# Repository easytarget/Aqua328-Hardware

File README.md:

# Controller for a Public (attended) aquarium

See the Full project log on:
https://hackaday.io/project/167871-aqua328-flexible-aquarium-controller

Software is in:
https://github.com/easytarget/Aqua328-Software

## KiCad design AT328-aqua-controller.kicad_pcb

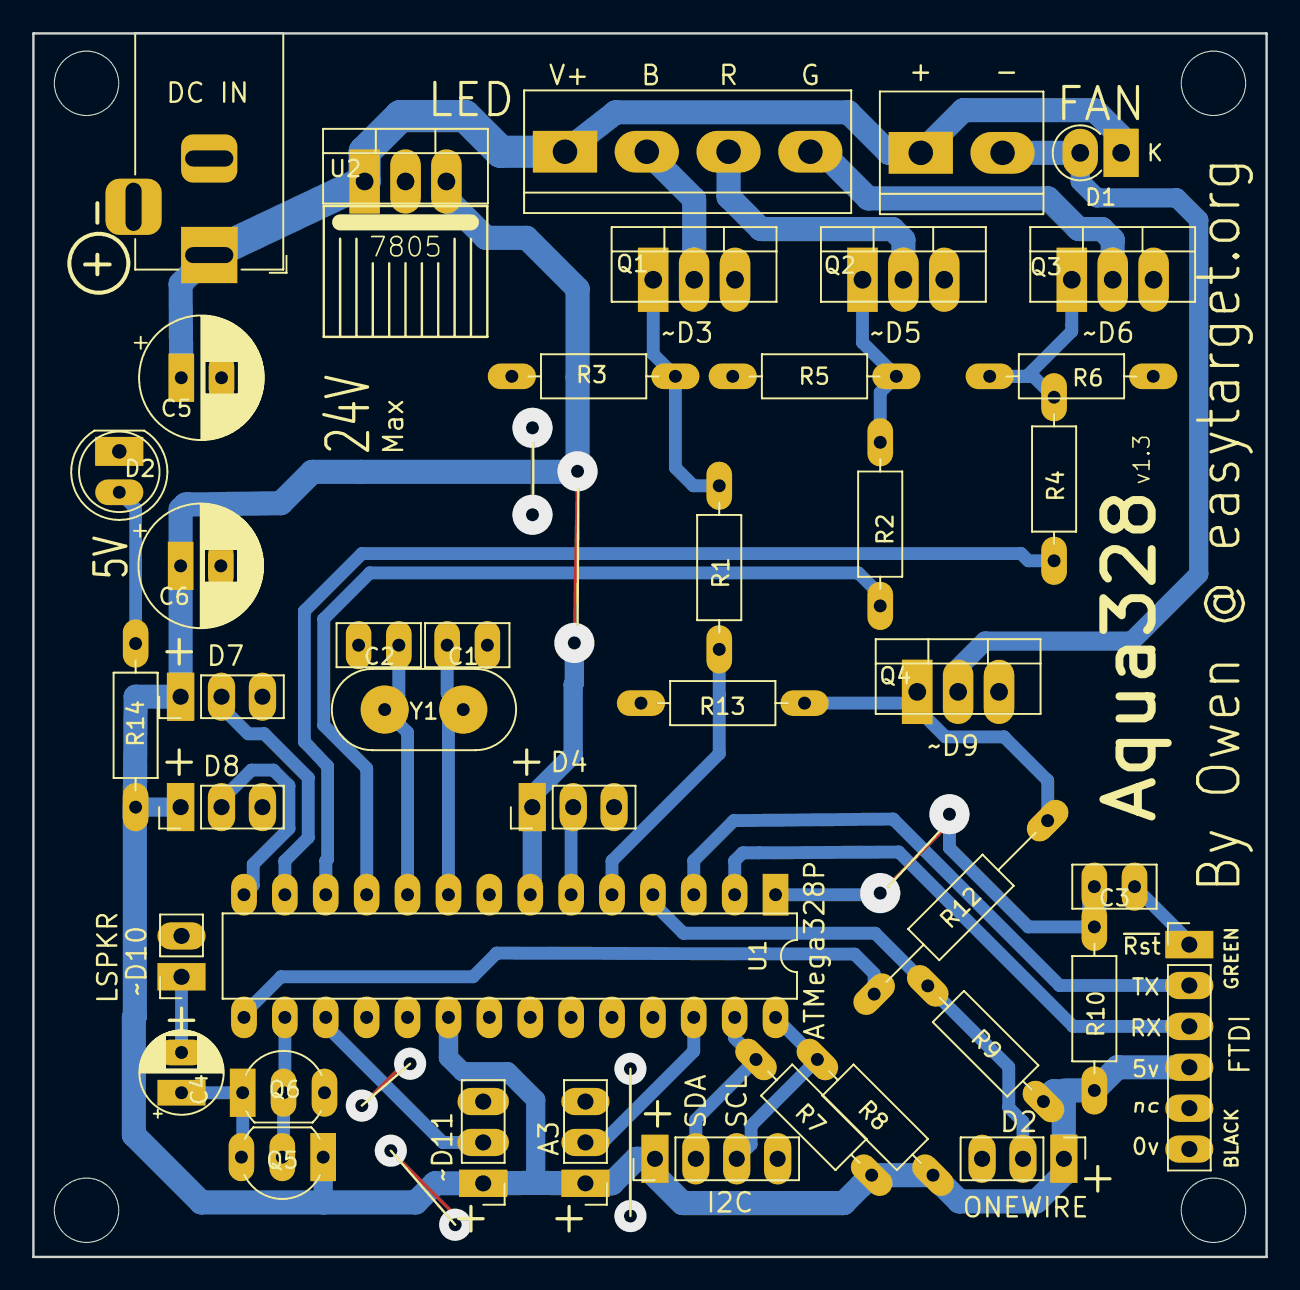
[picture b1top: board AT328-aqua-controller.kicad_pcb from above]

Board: 2 copper layers, 76.6 x 76.0 mm, 46 parts (0 on the bottom side), 33 nets.

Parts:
ABRG_LED1: LED-Strip; TerminalBlock_bornier-4_P5.08mm
AUX1, AUX2, AUX3: Aux Connector; PinHeader_1x03_P2.54mm_Vertical
BUTTON1: Lights/Cycle; PinHeader_1x03_P2.54mm_Vertical
C1, C2: 22p; C_Disc_D5.0mm_W2.5mm_P2.50mm
C3: 100nF; C_Disc_D5.0mm_W2.5mm_P2.50mm
C4: 470uF; CP_Radial_D5.0mm_P2.50mm
C5: 100uF; CP_Radial_D7.5mm_P2.50mm
C6: 22uF; CP_Radial_D7.5mm_P2.50mm
D1: 1N4007; D_DO-41_SOD81_P2.54mm_Vertical_KathodeUp
D2: 5v; LED_D5.0mm
DC_IN1: 12/24v; BarrelJack_Horizontal
FAN1: Fan PWM NPN; TerminalBlock_bornier-2_P5.08mm
FTDI1: FTDI Program Port; PinHeader_1x06_P2.54mm_Vertical
H1, H2, H3, H4: MountingHole; MountingHole_4mm
I2C1: Display; PinHeader_1x04_P2.54mm_Vertical
LID1: Lid Open; PinHeader_1x03_P2.54mm_Vertical
ONEWIRE1: Temp; PinHeader_1x03_P2.54mm_Vertical
Q1, Q2, Q3, Q4: IRL520N; TO-220-3_Vertical
Q5: BC337; TO-92_Inline_Wide
Q6: BC327; TO-92_Inline_Wide
R1, R2, R4, R14: 220R; R_Axial_DIN0207_L6.3mm_D2.5mm_P10.16mm_Horizontal
R3, R5, R6, R10, R13: 10K; R_Axial_DIN0207_L6.3mm_D2.5mm_P10.16mm_Horizontal
R7, R8, R9: 4K7; R_Axial_DIN0207_L6.3mm_D2.5mm_P10.16mm_Horizontal
R12: 220R; R_Axial_DIN0207_L6.3mm_D2.5mm_P15.24mm_Horizontal
SPKR1: Speaker; PinSocket_1x02_P2.54mm_Vertical
U1: ATmega328P-PU; DIP-28_W7.62mm
U2: LM7805_TO220; TO-220-3_Vertical
Y1: 16MHz; Crystal_HC49-4H_Vertical

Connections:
1WIRE: ONEWIRE1.2, R9.2, U1.4
+5V: AUX1.1, AUX2.1, AUX3.1, BUTTON1.1, C6.1, FTDI1.4, I2C1.1, LID1.1, ONEWIRE1.1, Q5.1, R7.1, R8.1, R9.1, R10.2, R14.1, U1.7, U1.20, U2.3
+VDC: ABRG_LED1.1, C5.1, D1.1, DC_IN1.1, FAN1.1, U2.1
AUX1: AUX1.2, U1.17
AUX2: AUX2.2, U1.26
AUX3: AUX3.2, U1.14
BUZZ: Q5.2, Q6.2, U1.16
CYCLE: BUTTON1.2, U1.6
FAN: R12.2, U1.15
GND: AUX1.3, AUX2.3, AUX3.3, BUTTON1.3, C1.1, C2.1, C5.2, C6.2, D2.1, DC_IN1.2, FTDI1.6, I2C1.4, LID1.3, ONEWIRE1.3, Q1.3, Q2.3, Q3.3, Q4.3, Q6.3, R3.2, R5.2, R6.2, R13.2, SPKR1.2, U1.8, U1.22, U2.2
LED-B: R1.2, U1.5
LED-G: R4.2, U1.12
LED-R: R2.2, U1.11
LID: LID1.2, U1.13
unnamed: ABRG_LED1.2, Q1.2
unnamed: ABRG_LED1.3, Q2.2
unnamed: ABRG_LED1.4, Q3.2
unnamed: C1.2, U1.9, Y1.1
unnamed: C2.2, U1.10, Y1.2
unnamed: C3.2, R10.1, U1.1
unnamed: C4.1, Q5.3, Q6.1
unnamed: C4.2, SPKR1.1
unnamed: D1.2, FAN1.2, Q4.2
unnamed: D2.2, R14.2
unnamed: Q1.1, R1.1, R3.1
unnamed: Q2.1, R2.1, R5.1
unnamed: Q3.1, R4.1, R6.1
unnamed: Q4.1, R12.1, R13.1
RESET: C3.1, FTDI1.1
RX: FTDI1.3, U1.2
SCL: I2C1.2, R7.2, U1.27
SDA: I2C1.3, R8.2, U1.28
TX: FTDI1.2, U1.3

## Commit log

2019-09-30 Initial; been in design for a while though.
2019-09-30 More IO and better PCB silk
2019-10-04 More PCB work, adding power to all pins, more io and better silk
2019-10-04 Bigger power terminals, all power wiring on one side, bigger power tracks
2019-10-15 Lots of minor tweaks to layout and silkscreen, possibly complete.
2019-10-15 Add a version to silkscreen
2019-10-16 Minor silkscreen issues
2019-10-27 PCB v1.3
2019-10-27 Start on V2 PCB, relocated and duplicated connectors, reset jumper.
2020-02-22 Case Stuff
2020-02-23 Adding a case and spacer for the LCD display
2020-02-27 Small redesign following prototype fitting. I'm fitting a speaker in place of the power jack, so I added a grill for that.
2020-03-09 Add links to Readme
2020-03-09 Ignore more
2020-04-11 New speaker circuit, updated PCB to suit and slight case mods.
2020-04-11 Document update
